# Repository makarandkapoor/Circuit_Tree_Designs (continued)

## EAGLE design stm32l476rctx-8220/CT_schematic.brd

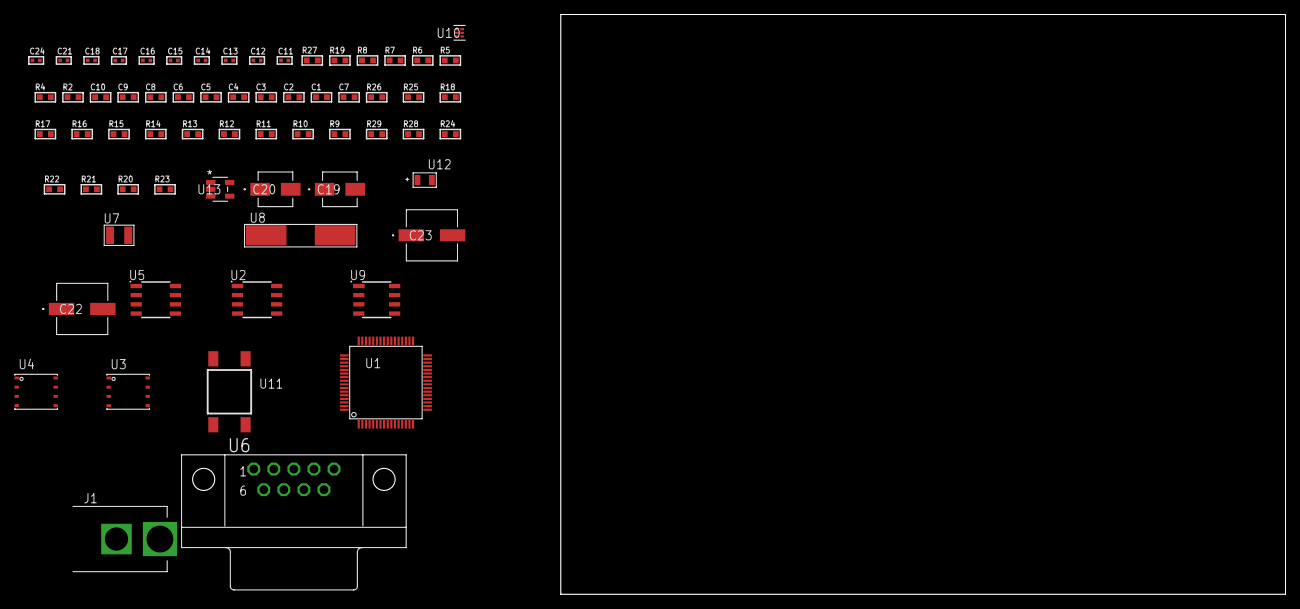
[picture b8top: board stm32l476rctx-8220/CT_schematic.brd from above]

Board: 2 copper layers, 100.0 x 80.0 mm, 65 parts (0 on the bottom side), 36 nets, no tracks yet.

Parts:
C1, C9: 1e-06; C0603
C2, C3, C4, C5, C6, C10: 1e-07; C0603
C7: 4.7e-06; C0603
C8: 1e-08; C0603
C11, C12, C13, C14: 1e-11; C0402
C15, C16, C17, C24: 1e-08; C0402
C18, C21: 1e-07; C0402
C19: 1e-06; EXV-9B
C20: 2.2e-06; EXV-9B
C22, C23: 0.0001; EXV-9H
J1: PJ-037B; PJ-037B_PACKAGE
R2: 1000.0; R0603
R4: 4700.0; R0603
R5, R6, R7, R8: 2200.0; R0603
R9, R10, R11, R12, R13, R14, R15, R16, R17, R18, R25, R26: 10000.0; R0603
R19: 120.0; R0603
R20: 470000.0; R0603
R21, R22, R24: 100000.0; R0603
R23: 164658.62; R0603
R27: 9100.0; R0603
R28: 680000.0; R0603
R29: 120000.0; R0603
U1: STM32L476RCT6; LQFP64
U2: AT25020B-SSHL-T; SOIC-8
U3: 24AA256-I/MF; DFN8-S
U4: 24AA512-I/MF; DFN8-S
U5: SN65HVD230D; SOIC-8
U6: 182-009-113R531; 182-009-MALE
U7: ABS07-32.768KHZ-7-T
U8: ABLS-25.000MHZ-B2F-T
U9: LP2954AIMX/NOPB; LP2954
U10: TPS3895ADRYR; SON-6
U11: 4-1437565-2; SW_4-1437565-2
U12: Q65110A2395; LGM67K-G1J2-24-Z
U13: nc7sz125m5x; NC7SZ125M5X

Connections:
CLK_CRYSTAL_U1_3: C11.1, U1.3, U7.1
CLK_CRYSTAL_U1_4: C12.1, U1.4, U7.2
CLK_CRYSTAL_U1_5: C13.1, U1.5, U8.1
CLK_CRYSTAL_U1_6: C14.1, U1.6, U8.2
GND: C1.2, C2.2, C3.2, C4.2, C5.2, C6.2, C7.2, C8.2, C9.2, C10.2, C11.2, C12.2, C13.2, C14.2, C15.2, C16.2, C17.2, C18.2, C19.2, C20.2, C21.2, C22.2, C23.2, C24.2, J1.2, R2.2, R9.2, R13.2, R16.2, R20.2, R24.2, R27.2, R29.2, U1.12, U1.18, U1.31, U1.47, U1.63, U2.4, U3.4, U4.4, U5.2, U6.5, U9.4, U10.2, U12.C, U13.1, U13.3
NET_U1_7: R4.1, U1.7, U13.4
NET_U1_29: R7.1, U1.29, U4.6
NET_U1_30: R8.1, U1.30, U4.5
NET_U1_58: R5.1, U1.58, U3.6
NET_U1_59: R6.1, U1.59, U3.5
NET_U1_60: R9.1, U1.60
NET_U1_62: U11.3, U11.4
NET_U2_3: R10.1, U2.3
NET_U2_7: R12.1, U2.7
NET_U3_1: R13.1, U3.1
NET_U3_2: R14.1, U3.2
NET_U3_3: R15.1, U3.3
NET_U4_1: R16.1, U4.1
NET_U4_2: R17.1, U4.2
NET_U4_3: R18.1, U4.3
NET_U5_6: R19.2, U5.6
NET_U5_8: R20.1, U5.8
NET_U6_2: R19.2, U5.6, U6.2
NET_U6_3: R19.1, U5.7, U6.3
NET_U9_3: R22.1, U9.3
NET_U9_5: R21.1, U9.5
NET_U9_7: R23.2, R24.1, U9.7
NET_U10_1: R26.1, R27.1, U10.1
NET_U10_3: R28.2, R29.1, U10.3
NET_U10_4: R25.1, U10.4, U13.2
NET_U11_1: R2.1, U11.1, U11.2
PROC_CAN1_RX: U1.44, U5.4
PROC_CAN1_TX: U1.45, U5.1
PROC_SPI1_NSS: R11.1, U2.1
VCC_S1_12V1: C19.1, C22.1, C23.1, J1.1, R22.2, U9.8
VCC_TIER1_3V3: C1.1, C2.1, C3.1, C4.1, C5.1, C6.1, C7.1, C8.1, C9.1, C10.1, C15.1, C16.1, C17.1, C18.1, C20.1, C21.1, C24.1, R4.2, R5.2, R6.2, R7.2, R8.2, R10.2, R11.2, R12.2, R14.2, R15.2, R17.2, R18.2, R21.2, R23.1, R25.2, R26.2, R28.1, U1.1, U1.13, U1.19, U1.32, U1.48, U1.64, U2.8, U3.7, U3.8, U4.7, U4.8, U5.3, U9.1, U10.6, U13.5
